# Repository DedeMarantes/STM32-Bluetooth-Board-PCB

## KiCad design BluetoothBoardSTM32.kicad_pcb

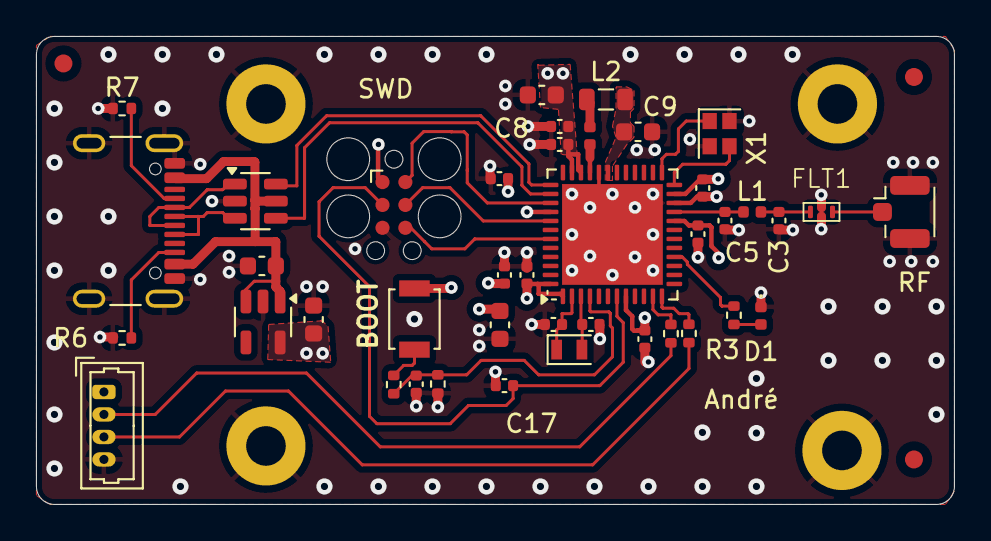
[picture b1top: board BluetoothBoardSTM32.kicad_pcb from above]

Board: 4 copper layers, 51.0 x 26.0 mm, 48 parts (0 on the bottom side), 28 nets.

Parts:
C1, C9, C13, C18, C19: 4.7uF; C_0603_1608Metric
C2, C4, C6, C8, C11, C12, C14, C15, C16, C17: 100nF; C_0402_1005Metric
C3: 0.8pF; C_0402_1005Metric
C5: 0.3pF; C_0402_1005Metric
C7, C10: 10pF; C_0402_1005Metric
D1: LED; LED_0402_1005Metric
FID1, FID2, FID3: Fiducial; Fiducial_1mm_Mask2mm
FLT1: DLF162500LT-5028A1
H1, H2, H3, H4: MountingHole_Pad; MountingHole_2.2mm_M2_Pad
J1: Conn_Coaxial; U.FL_Hirose_U.FL-R-SMT-1_Vertical
J2: Conn_01x04; Molex_PicoBlade_53047-0410_1x04_P1.25mm_Vertical
J3: Conn_ARM_SWD_TagConnect_TC2030; Tag-Connect_TC2030-IDC-FP_2x03_P1.27mm_Vertical
J4: USB_C_Receptacle_USB2.0_16P; USB_C_Receptacle_GCT_USB4105-xx-A_16P_TopMnt_Horizontal
L1: 2.7nH; L_0402_1005Metric
L2: 10uH; L_0805_2012Metric
L3: 10nH; L_0402_1005Metric
R1, R4, R5: 100; R_0402_1005Metric
R2, R6, R7: 5.1k; R_0402_1005Metric
R3: 220; R_0402_1005Metric
SW1: SW_Push; SW_SPST_B3U-1000P
U1: STM32WB55CEU6; QFN-48-1EP_7x7mm_P0.5mm_EP5.6x5.6mm
U2: USBLC6-2SC6; SOT-23-6
U3: MIC5365-3.3YD5; SOT-23-5
X1: 32MHz; Crystal_SMD_2016-4Pin_2.0x1.6mm
X2: 32.768kHz; Crystal_SMD_2012-2Pin_2.0x1.2mm

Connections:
+3.3V: C1.1, C4.1, C6.1, C8.1, C11.1, C12.1, C13.1, C14.1, C15.1, C16.1, C19.1, J2.1, J3.1 (VCC), SW1.1, U1.1 (VBAT), U1.8 (VDDA), U1.20 (VDD), U1.23 (VDDRF), U1.34 (VDDSMPS), U1.35 (VDD), U1.40 (VDDUSB), U1.48 (VDD), U3.5 (VOUT)
+5V: C18.1, J4.A4 (VBUS), J4.A9 (VBUS), J4.B4 (VBUS), J4.B9 (VBUS), U2.5 (VBUS), U3.1 (VIN), U3.3 (EN)
/BOOT0: C2.1, R1.2, R2.1, U1.4 (PH3)
/HSE_IN: U1.25 (OSC_IN), X1.1
/HSE_OUT: U1.24 (OSC_OUT), X1.3
/LSE_IN: C7.1, U1.2 (PC14), X2.1
/LSE_OUT: C10.1, U1.3 (PC15), X2.2
/RF: C5.1, L1.2, U1.21 (RF1)
/RF_ANT: FLT1.3 (OUT), J1.1 (In)
/RF_MATCH: C3.1, FLT1.1 (IN), L1.1
/SMPS_FB: C9.1, L2.2, U1.31 (VFBSMPS)
/SMPS_LX: L3.2, U1.33 (VLXSMPS)
/SWCLK: J3.4 (SWCLK), U1.41 (PA14)
/SWDIO: J3.2 (SWDIO), U1.39 (PA13)
/SWO: J3.6 (SWO), U1.43 (PB3)
/UART_RX: R5.1, U1.12 (PA3)
/UART_TX: R4.1, U1.11 (PA2)
/USB_CC2: J4.B5 (CC2), R6.2
/USB_D+: J4.A6 (D+), J4.B6 (D+), U1.38 (PA12), U2.3 (I/O2), U2.4 (I/O2)
/USB_D-: J4.A7 (D-), J4.B7 (D-), U1.37 (PA11), U2.1 (I/O1), U2.6 (I/O1)
GND: C1.2, C2.2, C3.2, C4.2, C5.2, C6.2, C7.2, C8.2, C9.2, C10.2, C11.2, C12.2, C13.2, C14.2, C15.2, C16.2, C17.1, C18.2, C19.2, D1.1 (K), FLT1.2 (GND), FLT1.4 (GND), H1.1, H2.1, H3.1, H4.1, J1.2 (Ext), J2.4, J3.5 (GND), J4.A1 (GND), J4.A12 (GND), J4.B1 (GND), J4.B12 (GND), J4.S1 (SHIELD), R2.2, R6.1, R7.1, U1.22 (VSSRF), U1.32 (VSSSMPS), U1.49 (VSS), U2.2 (GND), U3.2 (GND), X1.2, X1.4
unnamed: D1.2 (A), R3.2
unnamed: J2.2, R4.2
unnamed: J2.3, R5.2
unnamed: J4.A5 (CC1), R7.2
unnamed: L2.1, L3.1
unnamed: R1.1, SW1.2
unnamed: R3.1, U1.16 (PA7)

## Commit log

2024-11-05 adicionando arquivos
